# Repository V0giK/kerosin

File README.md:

# Kerosin – RC Jet Refueling System

&#x20;

---

## ✨ Projektübersicht

**Kerosin – RC Jet Refueling System** ist ein modulares Open-Source-System zur Betankung von Flugmodellen mit Kerosin. Es basiert auf einer Mikrocontroller-Lösung zur Überwachung und Steuerung des Tankvorgangs.

Die Steuerungseinheit ("Controller") befindet sich am Tank. Eine zweite Einheit ("Remote") mit Touchdisplay zeigt Messdaten an und löst Aktionen aus. Die Kommunikation erfolgt über RS-422.

Ziel ist eine robuste und automatisierte komfortabler Bedienung und sicherer Betankung.

---

## 🚀 Features

- **Controller (Arduino Nano)** direkt am Tank
- **Remote (ESP32)** mit Touchdisplay (JC8048W550)
- RS-422 Kommunikation (seriell)
- Automatischer Entleerungsvorgang bei Beuteltanks bei Erreichen des Abschaltdrucks
- Durchflusssensor (YF-S401) zur Kerosinerkennung beim Rückpumpen
- Drucksensor (30 psi, 1/8" NPT) zur Abschaltung
- Konfigurierbare Modelle mit individuell speicherbaren Parametern (Tanktyp, Volumen, Abschaltdruck, usw.)
- Zahnradpumpe für zuverlässige Befüllung und Rückförderung
- 3D-druckbare Komponenten & KiCad-Platinenlayout

---

## 📂 Projektstruktur

```
.
├── software/         # PlatformIO Projekte
│   ├── sTankTeil_Controller/   # Arduino Nano Code
│   └── sTankTeil_Remote/       # ESP32 Touchdisplay
├── kicad/            # KiCad-Schaltplan & Platine
├── 3d/               # 3D-Druckteile (STL, STEP)
├── LICENSE           # GPLv3 Lizenz
└── README.md         # Dieses Dokument
```

---

## 🧱 Komponenten

| Komponente       | Beschreibung                            |
| ---------------- | --------------------------------------- |
| Arduino Nano     | Hauptsteuerung (am Tank)                |
| ESP32            | Remote-Display (JC8048W550)             |
| RS-422 Treiber   | Serielle Verbindung Controller ⇄ Remote |
| Drucksensor      | 30psi Sensor mit 1/8" NPT Gewinde       |
| Durchflusssensor | YF-S401 zur Kerosinerkennung            |
| Zahnradpumpe     | Elektronisch gesteuert, rückförderfähig |

---

## 🔌 Hardwareaufbau

**Controller** ist direkt am Tank montiert und steuert:

- Drucksensor
- Durchflusssensor
- Zahnradpumpe

**Remote** zeigt Live-Daten über ein kapazitives 5.5" Touchdisplay an und erlaubt:

- Auswahl von Modellspeichern
- Anzeige von Druck, Durchfluss und der Menge des aktuellen Tankvorgangs
- Manuelle Aktionen und Steuerung

Verbindung erfolgt über abgeschirmtes RS-422-Kabel mit serieller Kommunikation.

---

## 📜 Lizenz

Dieses Projekt steht unter der [GNU General Public License v3.0](LICENSE). Jede Quellcodedatei enthält einen entsprechenden Lizenz-Header.

---

## 🤝 Mitmachen & Entwicklung

Pull Requests, Verbesserungsvorschläge oder Erweiterungen sind willkommen. Bei Fragen oder Problemen bitte [Issues](https://github.com/V0giK/kerosin/issues) verwenden.

---

## 🌍 Autor / Projekt

Entwickelt von [V0giK](https://github.com/V0giK) für RC-Tank- & Kerosinsysteme.

---

## 📌 Aktuelle Version

**v1.1.0** – 2026-10-18

| Komponente | Version |
|------------|---------|
| Controller (`sTankTeil_Controller`) | 1.1.0 |
| Remote (`sTankTeil_Remote`)        | 1.1.0 |

Eine detaillierte Übersicht aller Änderungen befindet sich in der [CHANGELOG.md](CHANGELOG.md).

---

> „This is not just fuel transfer – it's controlled refueling.“

---

während des bastelns ... https://youtube.com/shorts/paOjxJlpqOs

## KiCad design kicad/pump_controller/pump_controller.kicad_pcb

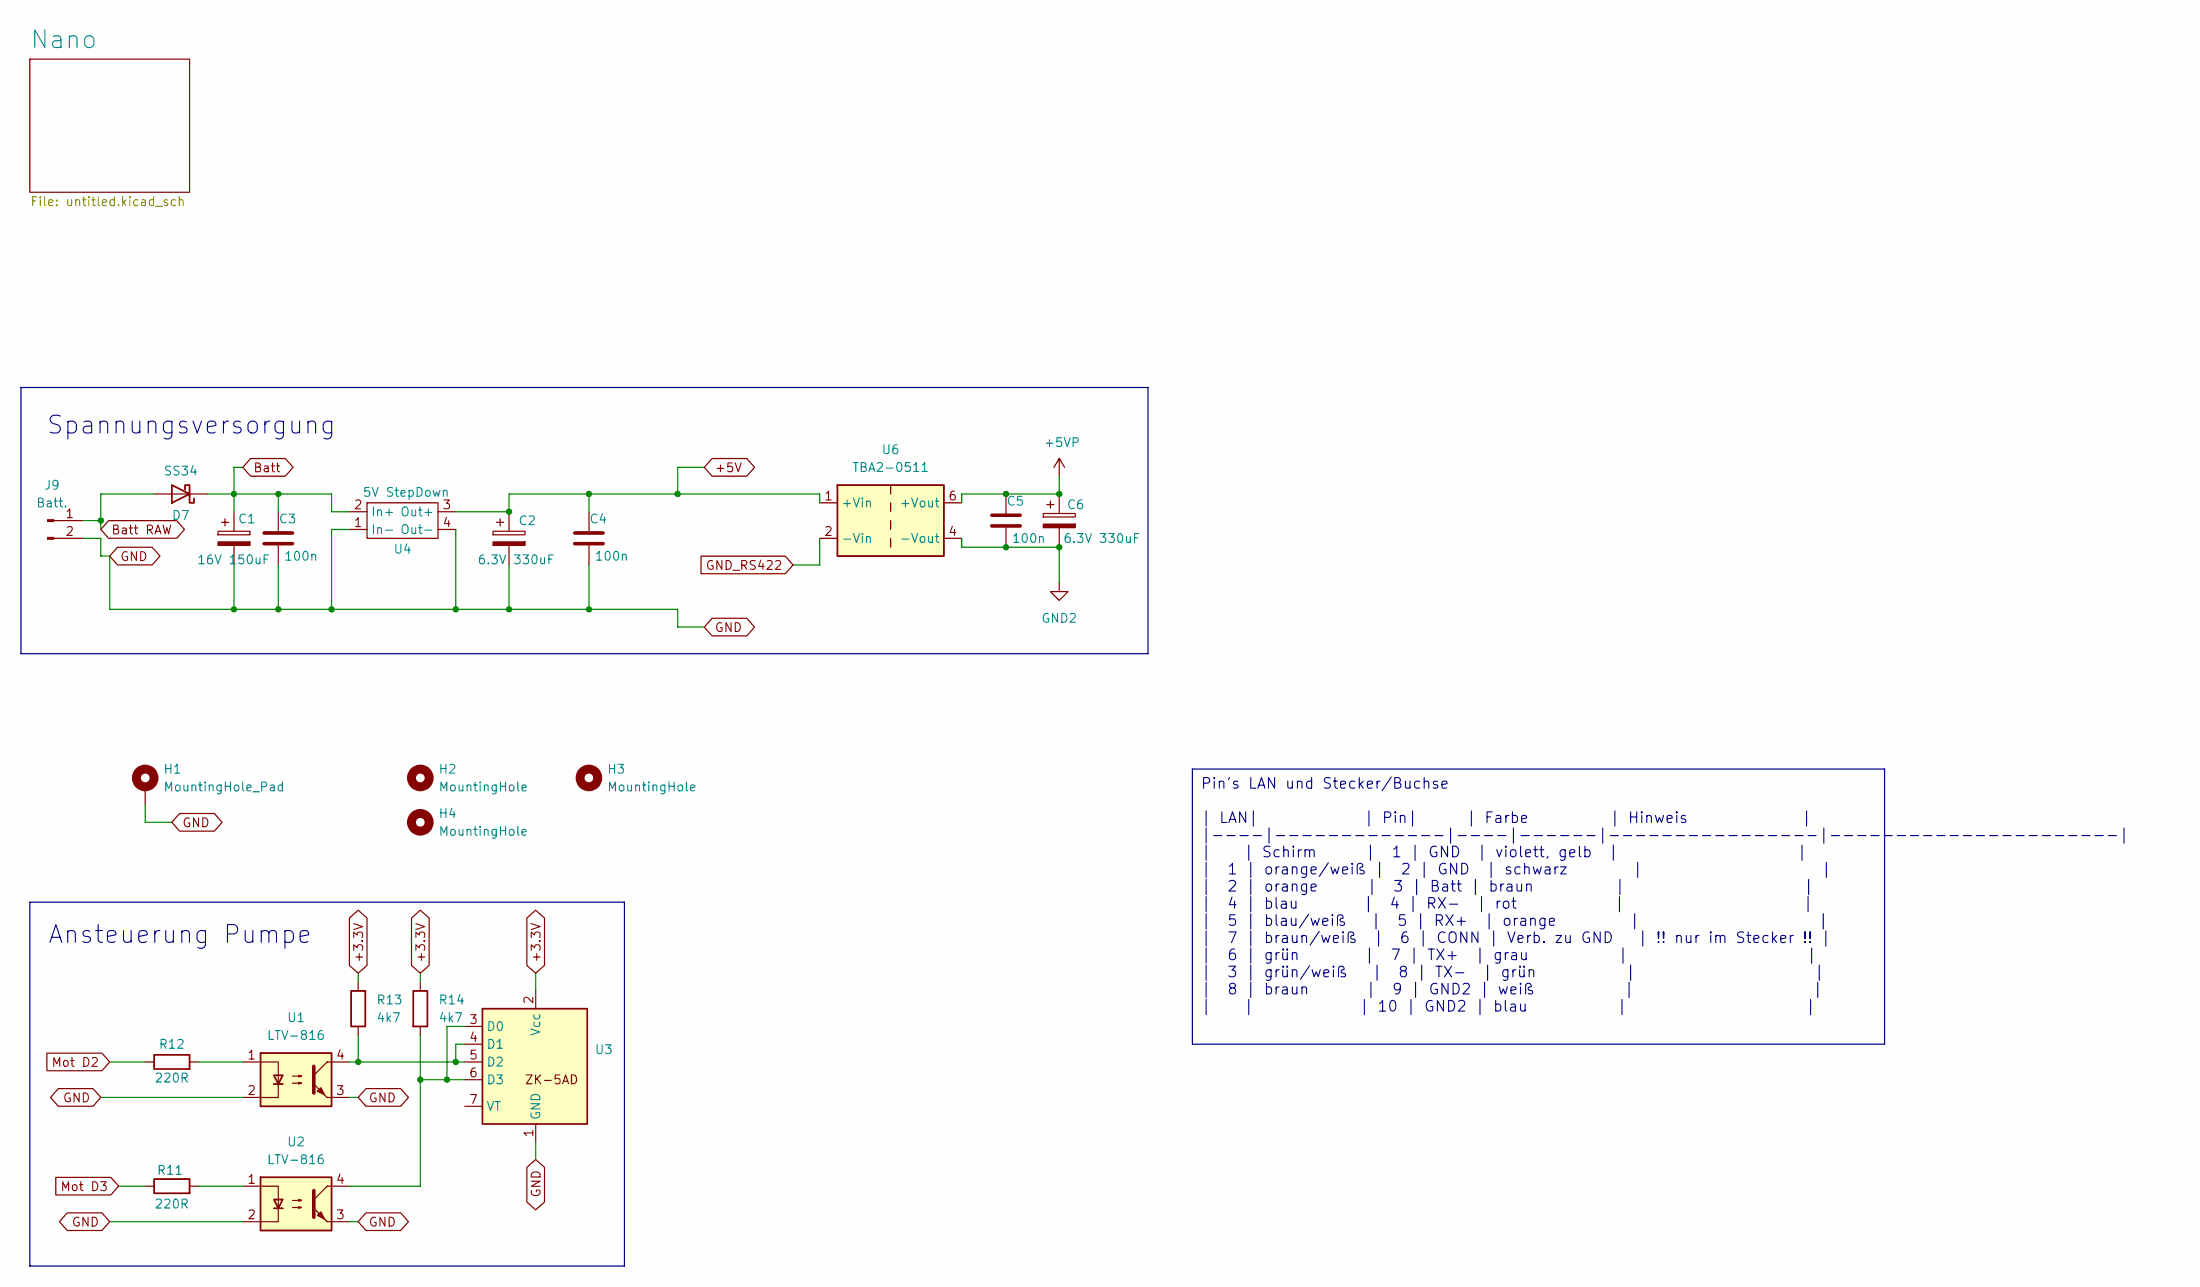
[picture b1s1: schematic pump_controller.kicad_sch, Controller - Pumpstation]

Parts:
C1: 16V 150uF; CP_EIA-7343-31_Kemet-D_Pad2.25x2.55mm_HandSolder
C2, C6: 6.3V 330uF; CP_EIA-7343-31_Kemet-D_Pad2.25x2.55mm_HandSolder
C3, C4, C5: 100n; C_0805_2012Metric_Pad1.18x1.45mm_HandSolder
D7: SS34; D_SMA
H1: MountingHole_Pad; MountingHole_3.2mm_M3_Pad_Via
H2, H4: MountingHole; MountingHole_3.2mm_M3_ISO7380
H3: MountingHole; MountingHole_3.5mm
J9: Batt.; PinHeader_1x02_P2.54mm_Vertical
R11, R12: 220R; R_0805_2012Metric_Pad1.20x1.40mm_HandSolder
R13, R14: 4k7; R_0805_2012Metric_Pad1.20x1.40mm_HandSolder
U1, U2: LTV-816; SMD-4_4.6x7.62mm_P2.54mm
U3: AK-5AD_dual_H-Bridge
U4: 5V StepDown; Step-Down 5V
U6: TBA2-0511; Converter_DCDC_TRACO_TBA2-xxxx_Single_THT

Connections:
+3.3V: R13.2, R14.1, U3.2 (Vcc)
+5V: C2.1, C4.1, U4.3 (Out+), U6.1 (+Vin); also elsewhere on the board
+5VP: C5.1, C6.1, U6.6 (+Vout); also elsewhere on the board
Batt: C1.1, C3.1, D7.1 (K), U4.2 (In+); also elsewhere on the board
Batt RAW: D7.2 (A), J9.1
GND: C1.2, C2.2, C3.2, C4.2, H1.1, J9.2, U1.2, U1.3, U2.2, U2.3, U3.1 (GND), U4.1 (In-), U4.4 (Out-); also elsewhere on the board
GND2: C5.2, C6.2, U6.4 (-Vout); also elsewhere on the board
GND_RS422: U6.2 (-Vin); also elsewhere on the board
Mot D2: R12.1; also elsewhere on the board
Mot D3: R11.1; also elsewhere on the board
unnamed: R11.2, U2.1
unnamed: R12.2, U1.1
unnamed: R14.2, U2.4, U3.3 (D0), U3.6 (D3)
unnamed: R13.1, U1.4, U3.4 (D1), U3.5 (D2)

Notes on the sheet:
Spannungsversorgung
Ansteuerung Pumpe
Pin's LAN und Stecker/Buchse | LAN| | Pin| | Farbe | Hinweis | |----|-------------|----|------|----------------|----------------------| | | Schirm | 1 | GND | violett, gelb | | | 1 | orange/weiß | 2 | GND | schwarz | | | 2 | orange | 3 | Batt | braun | | | 4 | blau | 4 | RX- | rot | | | 5 | blau/we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

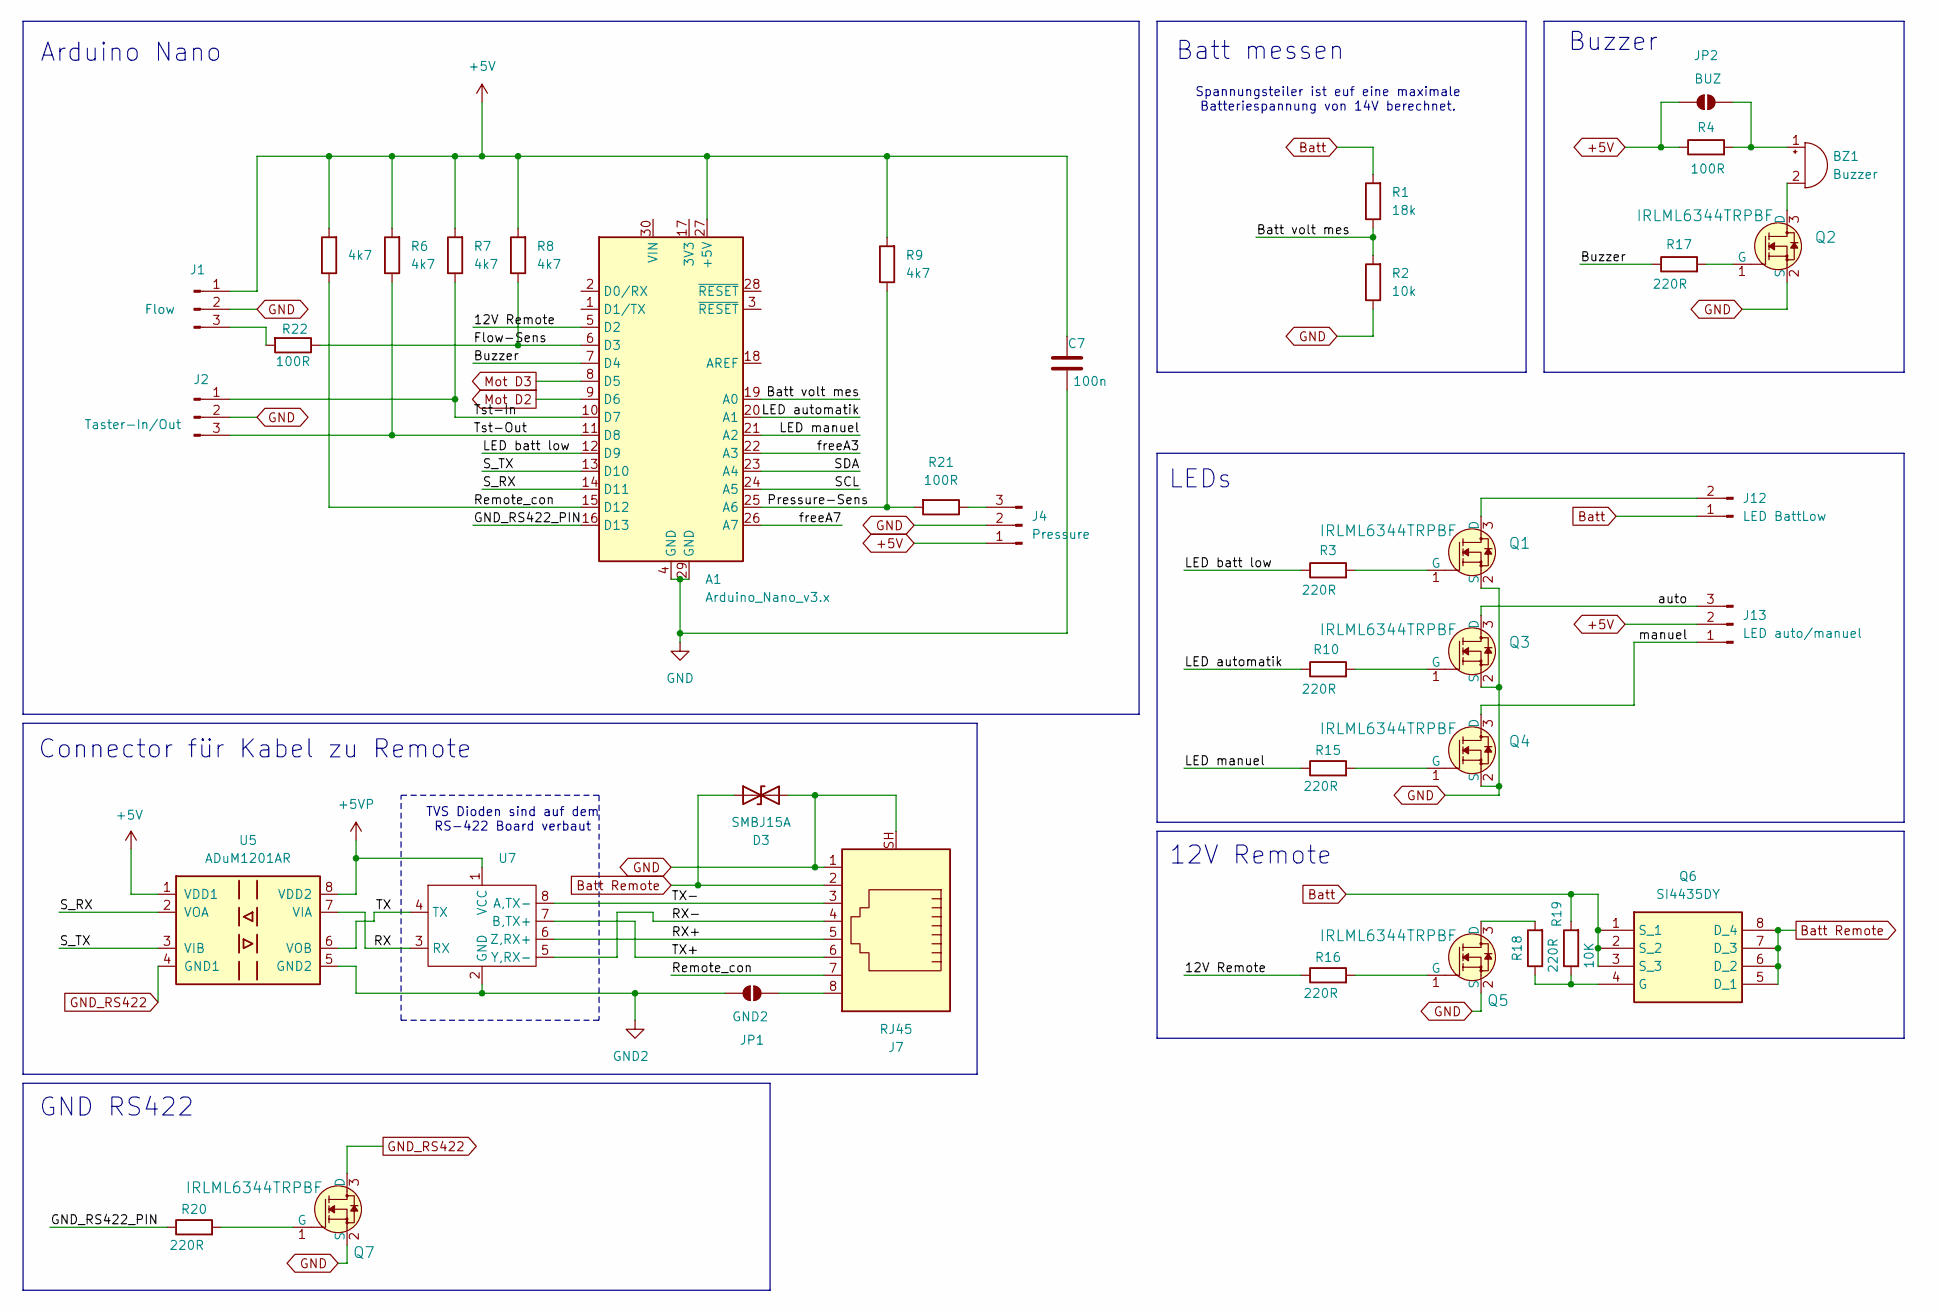
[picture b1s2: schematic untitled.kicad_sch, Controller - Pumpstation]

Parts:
A1: Arduino_Nano_v3.x; Arduino_Nano
BZ1: Buzzer; Buzzer_12x9.5RM6.7
C7: 100n; C_0805_2012Metric_Pad1.18x1.45mm_HandSolder
D3: SMBJ15A; D_SMB_Handsoldering
J1: Flow; JST_XH_B3B-XH-AM_1x03_P2.50mm_Vertical
J2: Taster-In/Out; PinHeader_1x03_P2.54mm_Vertical
J4: Pressure; JST_XH_B3B-XH-AM_1x03_P2.50mm_Vertical
J7: RJ45; RJ45_RCH_RC01937
J12: LED BattLow; PinHeader_1x02_P2.54mm_Vertical
J13: LED auto/manuel; PinHeader_1x03_P2.54mm_Vertical
JP1: GND2; SolderJumper-2_P1.3mm_Open_Pad1.0x1.5mm
JP2: BUZ; SolderJumper-2_P1.3mm_Open_Pad1.0x1.5mm
Q1, Q2, Q3, Q4, Q5, Q7: IRLML6344TRPBF; SOT-23-3; MPN IRLML6344TRPBF; Digi-Key_PN IRLML6344TRPBFCT-ND
Q6: SI4435DY; SOIC-8_5.3x6.2mm_P1.27mm; Mouser Part Number 512-SI4435DY
R1: 18k; R_0805_2012Metric_Pad1.20x1.40mm_HandSolder
R2: 10k; R_0805_2012Metric_Pad1.20x1.40mm_HandSolder
R3, R10, R15, R16, R17, R18, R20: 220R; R_0805_2012Metric_Pad1.20x1.40mm_HandSolder
R4, R21, R22: 100R; R_0805_2012Metric_Pad1.20x1.40mm_HandSolder
R5, R6, R7, R8, R9: 4k7; R_0805_2012Metric_Pad1.20x1.40mm_HandSolder
R19: 10K; R_0805_2012Metric_Pad1.20x1.40mm_HandSolder
U5: ADuM1201AR; SOIC-8_3.9x4.9mm_P1.27mm
U7: QYF-998_RS-422

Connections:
+5V: A1.27 (+5V), C7.1, J1.1, J4.1, J13.2, JP2.2 (B), R4.1, R5.2, R6.2, R7.2, R8.2, R9.2, U5.1 (VDD1); also elsewhere on the board
+5VP: U5.8 (VDD2), U7.1 (VCC); also elsewhere on the board
/Nano/12V Remote: A1.5 (D2), R16.1
/Nano/Batt volt mes: A1.19 (A0), R1.1, R2.2
/Nano/Buzzer: A1.7 (D4), R17.1
/Nano/Flow-Sens: A1.6 (D3), R8.1, R22.1
/Nano/GND_RS422_PIN: A1.16 (D13), R20.1
/Nano/LED automatik: A1.20 (A1), R10.1
/Nano/LED batt low: A1.12 (D9), R3.1
/Nano/LED manuel: A1.21 (A2), R15.1
/Nano/Pressure-Sens: A1.25 (A6), R9.1, R21.2
/Nano/RX: U5.7 (VIA), U7.3 (RX)
/Nano/RX+: J7.4, U7.5 (Y)
/Nano/RX-: J7.5, U7.6 (Z)
/Nano/Remote_con: A1.15 (D12), J7.7, R5.1
/Nano/SCL: A1.24 (A5)
/Nano/SDA: A1.23 (A4)
/Nano/S_RX: A1.14 (D11), U5.2 (VOA)
/Nano/S_TX: A1.13 (D10), U5.3 (VIB)
/Nano/TX: U5.6 (VOB), U7.4 (TX)
/Nano/TX+: J7.6, U7.7 (B)
/Nano/TX-: J7.3, U7.8 (A)
/Nano/Tst-In: A1.10 (D7), J2.1, R7.1
/Nano/Tst-Out: A1.11 (D8), J2.3, R6.1
/Nano/auto: J13.3, Q3.3 (D)
/Nano/freeA3: A1.22 (A3)
/Nano/freeA7: A1.26 (A7)
/Nano/manuel: J13.1, Q4.3 (D)
Batt: J12.1, Q6.1 (S_1), Q6.2 (S_2), Q6.3 (S_3), R1.2, R19.2; also elsewhere on the board
Batt Remote: D3.1 (A1), J7.2, Q6.5 (D_1), Q6.6 (D_2), Q6.7 (D_3), Q6.8 (D_4)
GND: A1.4 (GND), A1.29 (GND), C7.2, D3.2 (A2), J1.2, J2.2, J4.2, J7.1, J7.SH, Q1.2 (S), Q2.2 (S), Q3.2 (S), Q4.2 (S), Q5.2 (S), Q7.2 (S), R2.1; also elsewhere on the board
GND2: JP1.1 (A), U5.5 (GND2), U7.2 (GND); also elsewhere on the board
GND_RS422: Q7.3 (D), U5.4 (GND1); also elsewhere on the board
Mot D2: A1.9 (D6); also elsewhere on the board
Mot D3: A1.8 (D5); also elsewhere on the board
unnamed: BZ1.1 (+), JP2.1 (A), R4.2
unnamed: BZ1.2 (-), Q2.3 (D)
unnamed: J1.3, R22.2
unnamed: J4.3, R21.1
unnamed: J12.2, Q1.3 (D)
unnamed: J7.8, JP1.2 (B)
unnamed: Q1.1 (G), R3.2
unnamed: Q2.1 (G), R17.2
unnamed: Q3.1 (G), R10.2
unnamed: Q4.1 (G), R15.2
unnamed: Q5.3 (D), R18.2
unnamed: Q5.1 (G), R16.2
unnamed: Q6.4 (G), R18.1, R19.1
unnamed: Q7.1 (G), R20.2

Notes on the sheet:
Buzzer
GND RS422
12V Remote
LEDs
Spannungsteiler ist euf eine maximale Batteriespannung von 14V berechnet.
TVS Dioden sind auf dem RS-422 Board verbaut
Batt messen
Arduino Nano
Connector für Kabel zu Remote

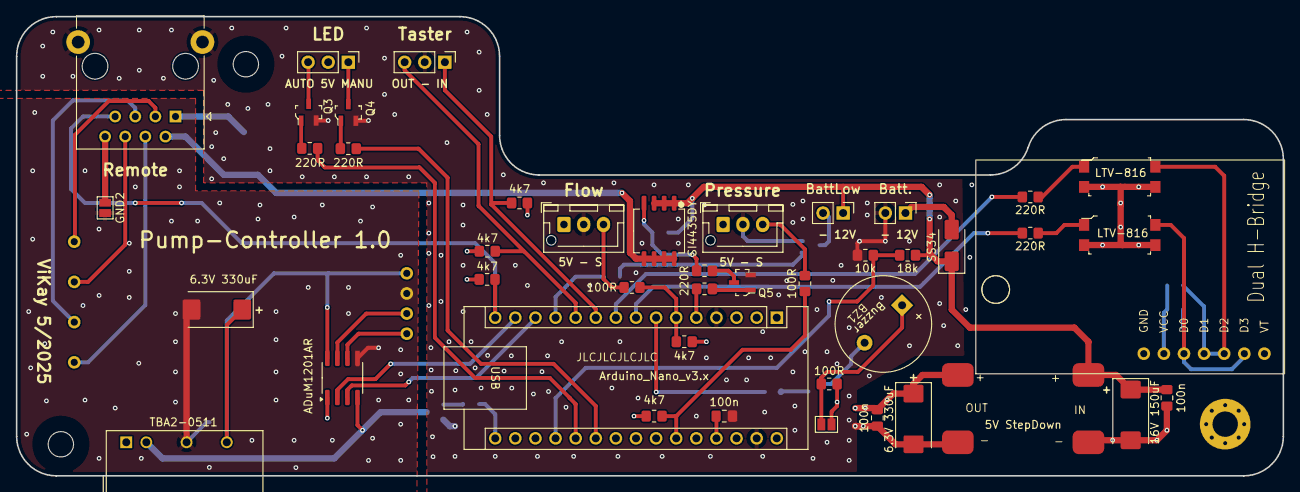
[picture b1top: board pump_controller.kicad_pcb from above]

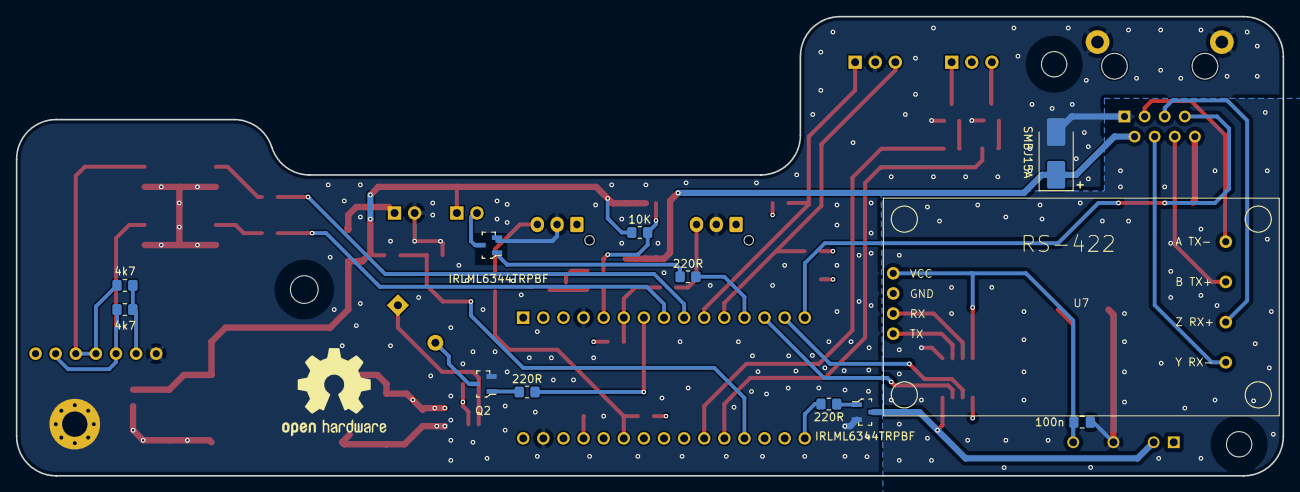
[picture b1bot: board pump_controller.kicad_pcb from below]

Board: 4 copper layers, 160.0 x 58.0 mm, 60 parts (12 on the bottom side), 51 nets.

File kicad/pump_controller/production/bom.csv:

Designator,Footprint,Quantity,Value,LCSC Part #
A1,Arduino_Nano,1,Arduino_Nano_v3.x,
BZ1,Buzzer_12x9.5RM6.7,1,Buzzer,
C1,CP_EIA-7343-31_Kemet-D_Pad2.25x2.55mm_HandSolder,1,16V 150uF,
"C2, C6",CP_EIA-7343-31_Kemet-D_Pad2.25x2.55mm_HandSolder,2,6.3V 330uF,
"C3, C4, C5, C7",0805,4,100n,
D3,D_SMB_Handsoldering,1,SMBJ15A,
D7,D_SMA,1,SS34,
J1,JST_XH_B3B-XH-AM_1x03_P2.50mm_Vertical,1,Flow,
J12,PinHeader_1x02_P2.54mm_Vertical,1,LED BattLow,
J13,PinHeader_1x03_P2.54mm_Vertical,1,LED auto/manuel,
J2,PinHeader_1x03_P2.54mm_Vertical,1,Taster-In/Out,
J4,JST_XH_B3B-XH-AM_1x03_P2.50mm_Vertical,1,Pressure,
J7,RJ45_RCH_RC01937,1,RJ45,
J9,PinHeader_1x02_P2.54mm_Vertical,1,Batt.,
"Q1, Q2, Q3, Q4, Q5, Q7",SOT-23-3,6,IRLML6344TRPBF,IRLML6344TRPBF
Q6,SOIC-8_5.3x6.2mm_P1.27mm,1,SI4435DY,
R1,0805,1,18k,
"R10, R11, R12, R15, R16, R17, R18, R20, R3",0805,9,220R,
"R13, R14, R5, R6, R7, R8, R9",0805,7,4k7,
"R19, R2",0805,2,10K,
"R21, R22, R4",0805,3,100R,
"U1, U2",SMD-4_4.6x7.62mm_P2.54mm,2,LTV-816,
U3,AK-5AD_dual_H-Bridge,1,~,
U5,SOIC-8_3.9x4.9mm_P1.27mm,1,ADuM1201AR,
U6,Converter_DCDC_TRACO_TBA2-xxxx_Single_THT,1,TBA2-0511,
U7,QYF-998_RS-422,1,~,

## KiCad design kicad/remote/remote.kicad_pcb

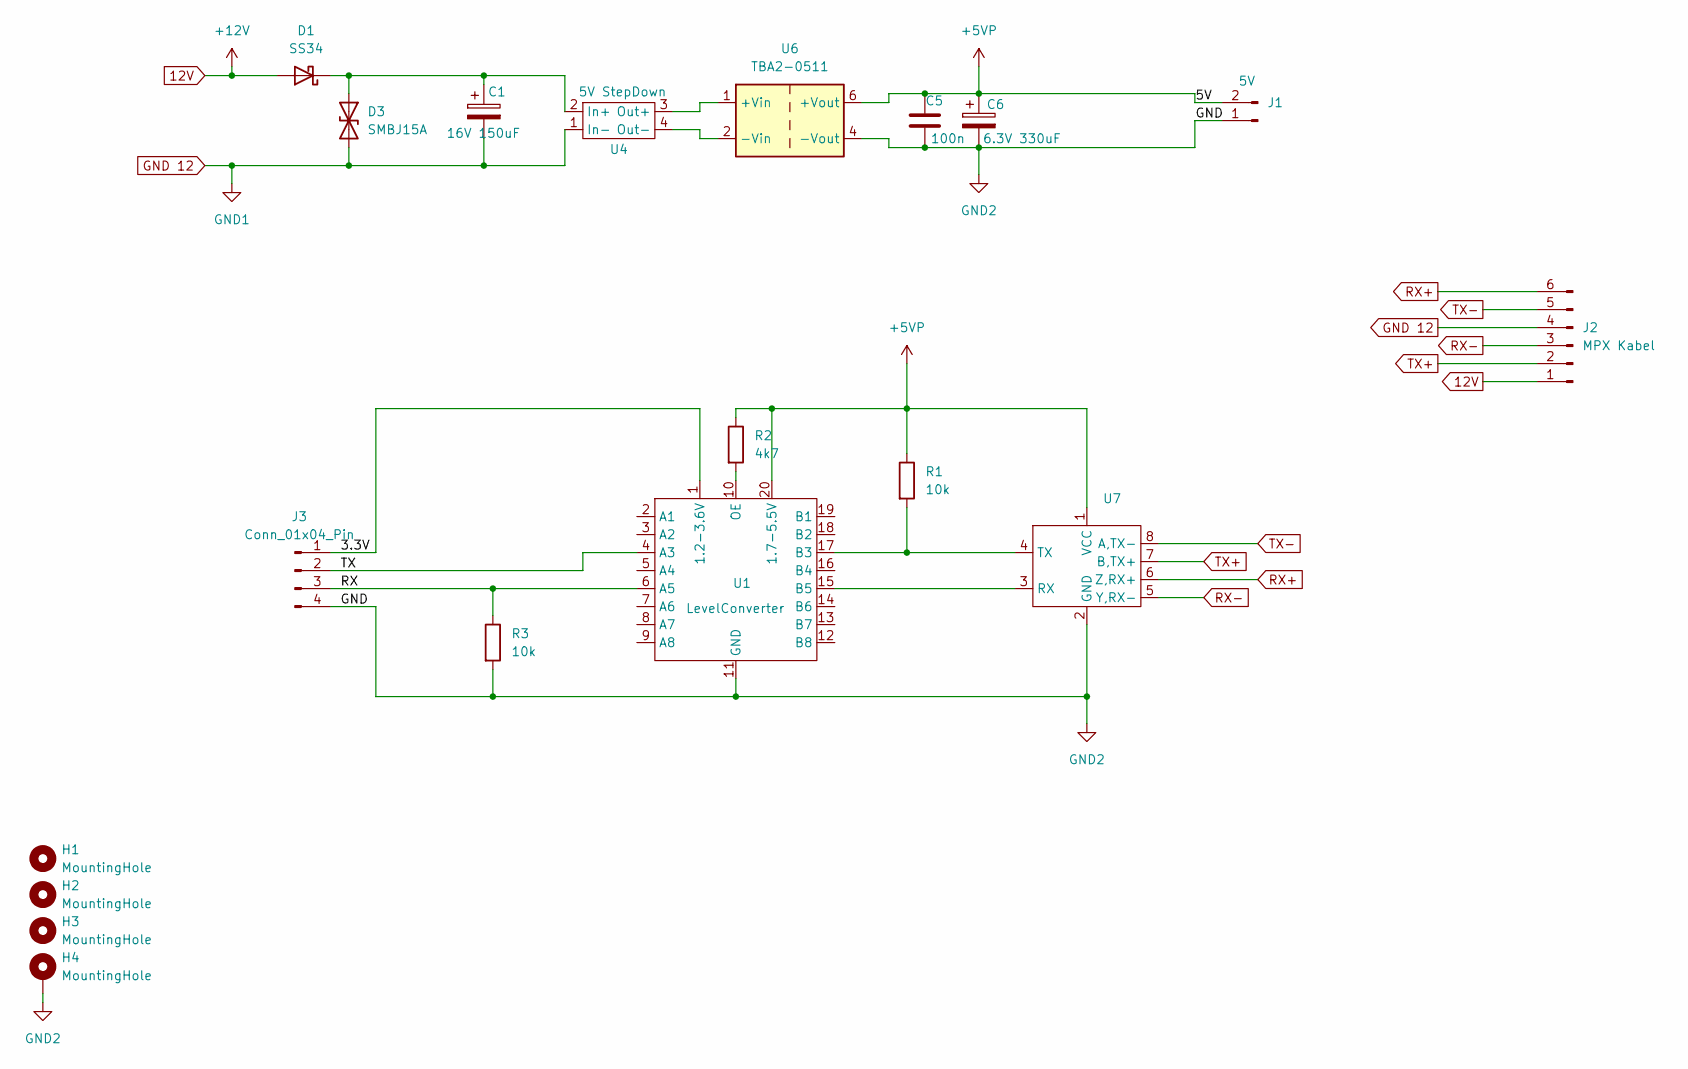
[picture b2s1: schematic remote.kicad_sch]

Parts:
C1: 16V 150uF; CP_EIA-7343-31_Kemet-D_Pad2.25x2.55mm_HandSolder
C5: 100n; C_0805_2012Metric_Pad1.18x1.45mm_HandSolder
C6: 6.3V 330uF; CP_EIA-7343-31_Kemet-D_Pad2.25x2.55mm_HandSolder
D1: SS34; D_SMA
D3: SMBJ15A; D_SMB_Handsoldering
H1, H2, H3: MountingHole; MountingHole_3.2mm_M3_ISO7380
H4: MountingHole; MountingHole_3.2mm_M3_Pad_Via
J1: 5V; PinHeader_1x02_P2.54mm_Vertical
J2: MPX Kabel; MPX_Adapter_small_6Pol
J3: Conn_01x04_Pin; PinHeader_1x04_P2.54mm_Vertical
R1, R3: 10k; R_Axial_DIN0207_L6.3mm_D2.5mm_P10.16mm_Horizontal
R2: 4k7; R_Axial_DIN0207_L6.3mm_D2.5mm_P10.16mm_Horizontal
U1: LevelConverter; LevelConversion_TXB0108
U4: 5V StepDown; Step-Down 5V
U6: TBA2-0511; TBA2-xxxx_liegend
U7: QYF-998_RS-422

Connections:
12V: D1.2 (A), J2.1
+5VP: C5.1, C6.1, J1.2, R1.1, R2.1, U1.20 (1.7-5.5V), U6.6 (+Vout), U7.1 (VCC)
/3.3V: J3.1, U1.1 (1.2-3.6V)
/RX: J3.3, R3.1, U1.6 (A5)
/TX: J3.2, U1.4 (A3)
GND2: C5.2, C6.2, H4.1, J1.1, J3.4, R3.2, U1.11 (GND), U6.4 (-Vout), U7.2 (GND)
GND 12: C1.2, D3.2 (A2), J2.4, U4.1 (In-)
unnamed: C1.1, D1.1 (K), D3.1 (A1), U4.2 (In+)
unnamed: R1.2, U1.17 (B3), U7.4 (TX)
unnamed: U1.15 (B5), U7.3 (RX)
unnamed: R2.2, U1.10 (OE)
unnamed: U4.3 (Out+), U6.1 (+Vin)
unnamed: U4.4 (Out-), U6.2 (-Vin)
RX+: J2.6, U7.6 (Z,RX+)
RX-: J2.3, U7.5 (Y,RX-)
TX+: J2.2, U7.7 (B,TX+)
TX-: J2.5, U7.8 (A,TX-)

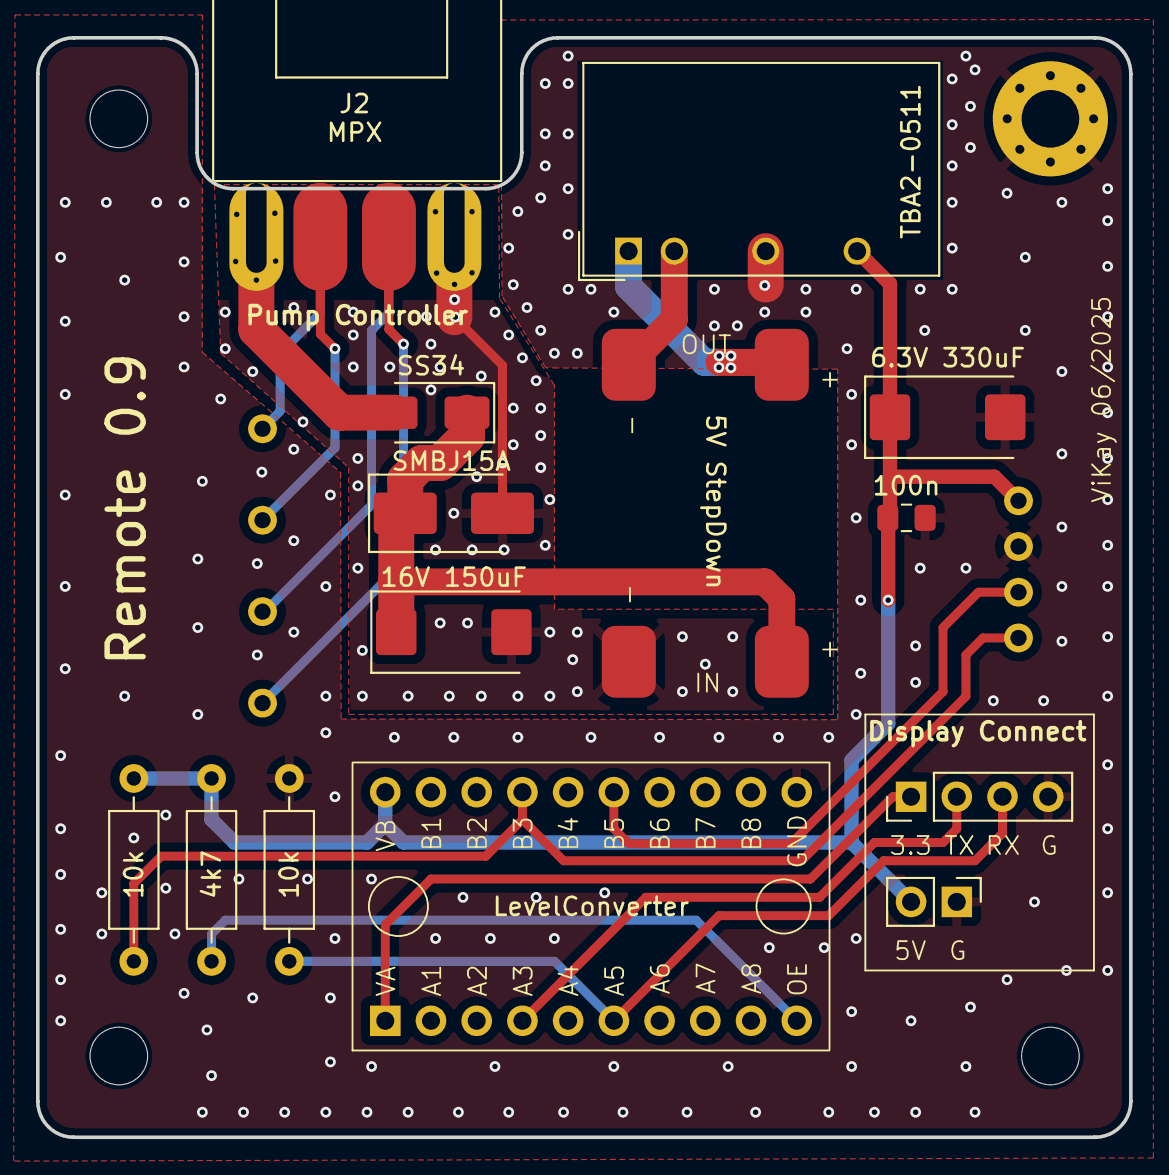
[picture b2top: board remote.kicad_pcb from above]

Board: 2 copper layers, 60.7 x 61.1 mm, 19 parts (1 on the bottom side), 17 nets.

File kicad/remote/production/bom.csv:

Designator,Footprint,Quantity,Value,LCSC Part #
C1,CP_EIA-7343-31_Kemet-D_Pad2.25x2.55mm_HandSolder,1,16V 150uF,
C5,0805,1,100n,
C6,CP_EIA-7343-31_Kemet-D_Pad2.25x2.55mm_HandSolder,1,6.3V 330uF,
D1,D_SMA,1,SS34,
D3,D_SMB_Handsoldering,1,SMBJ15A,
J1,PinHeader_1x02_P2.54mm_Vertical,1,5V,
J2,MPX_Adapter_small_6Pol,1,MPX Kabel,
J3,PinHeader_1x04_P2.54mm_Vertical,1,Conn_01x04_Pin,
"R1, R3",R_Axial_DIN0207_L6.3mm_D2.5mm_P10.16mm_Horizontal,2,10k,
R2,R_Axial_DIN0207_L6.3mm_D2.5mm_P10.16mm_Horizontal,1,4k7,
U1,LevelConversion_TXB0108,1,LevelConverter,
U6,TBA2-xxxx_liegend,1,TBA2-0511,
U7,QYF-998_RS-422,1,~,

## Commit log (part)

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2025-05-12 Update issue templates
2025-08-14 Add existing PlatformIO and KiCad data
2025-08-14 rename code -> software
2025-08-14 cleanup
2025-08-14 LICENCE
2025-08-14 3D-Files
2025-08-14 README
2025-08-14 KiCad clean
2025-08-15 code cleanup, tiny fixes
2025-08-15 new defaukt batcalibration factor
2025-08-16 Serlial.print's entfernt
2025-08-16 fix check model is available
2025-08-16 Watchdog
2025-08-16 flush LittleFS
2025-08-16 uart opimierung
2025-08-17 optimiert
2025-08-17 snake
2025-08-17 Dialog Kalibrierung Spannungsmessung
2025-08-17 kicad gerber files
2025-08-19 fix wdt
2025-08-19 something
2025-08-20 settings menu screen entfernt
2025-08-20 fix enttank mengenberechnung
2025-08-27 refactor: Codestruktur verbessert für bessere Übersichtlichkeit und Wartbarkeit
2025-08-27 refactor
2025-08-29 initial
2025-08-29 feat: backup / ota
2025-08-29 feat: captive portal
2025-08-30 refactor style
2025-08-30 Update ToDo list in README.md
    Removed OTA and backup tasks from ToDo list.
2025-08-30 Fix grammar in README.md
2025-08-30 Simplify communication description in README
2025-08-31 feat: Abschaltzeit
2025-08-31 Remove a ToDo item from README
2025-08-31 feat: version inf
2025-08-31 Remove ToDo section from README
    Removed the ToDo section from the README.
2025-09-01 style: kringel
2025-09-01 feat: aeroBlocks, heartbeat
2025-09-01 fix: config save
2025-09-06 Add image pump_fertig.jpg to README
2025-09-08 feat: add Druck and Diff. Druck labels to pump screen and update their values
2025-09-08 refactor: LVGL Memory, PSRAM, LVGL-Caches, LVGL Refresh-Rate, Draw Layer Buffer, Modell-UI-Elemente begrenzen
2025-09-08 fix: disable debug output for cleaner execution
2025-09-08 refactor: consolidate UI flags into a union for improved maintainability and consistency
2025-09-08 chore: update software version to 1.1.1
2025-09-08 fix: downgrade software version from 1.1.1 to 1.1.0
2025-09-08 Refactor/refactor (#7)
    * refactor: LVGL Memory, PSRAM, LVGL-Caches, LVGL Refresh-Rate, Draw Layer Buffer, Modell-UI-Elemente begrenzen
    * fix: disable debug output for cleaner execution
    * refactor: consolidate UI flags into a union for improved maintainability and consistency
2025-09-08 fix: fix backup mode with OTA support and related flags
2025-09-08 fix: fix backup mode with OTA support and related flags (#8)
2025-09-08 chore: update software version to 1.1.0-beta
2025-09-08 Fix/ota (#9)
    * fix: fix backup mode with OTA support and related flags
    * chore: update software version to 1.1.0-beta
2025-09-08 Refactor/refactor (#10)
    * refactor: LVGL Memory, PSRAM, LVGL-Caches, LVGL Refresh-Rate, Draw Layer Buffer, Modell-UI-Elemente begrenzen
    * fix: disable debug output for cleaner execution
    * refactor: consolidate UI flags into a union for improved maintainability and consistency
    * chore: update software version to 1.1.1
    * fix: downgrade software version from 1.1.1 to 1.1.0
2025-09-09 refactor: update PumpSequence to use fixed-size array and simplify constructor; modify buffer functions for better memory handling; update software version to 1.0.1
2025-09-09 refactor: remove debug flag from UartCommunication constructor; increase buffer size in recData struct; update debug output handling across multiple files
2025-09-09 refactor: streamline loop logic for activity detection and update LED status
2025-09-09 Refactor/comtroller (#11)
    * refactor: update PumpSequence to use fixed-size array and simplify constructor; modify buffer functions for better memory handling; update software version to 1.0.1
    * refactor: remove debug flag from UartCommunication constructor; increase buffer size in recData struct; update debug output handling across multiple files
    * refactor: streamline loop logic for activity detection and update LED status
